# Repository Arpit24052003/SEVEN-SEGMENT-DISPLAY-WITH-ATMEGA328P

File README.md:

# SEVEN-SEGMENT-DISPLAY-WITH-ATMEGA328P
IN THIS PROJECT I HAVE INTERFACED TWO SEVEN SEGMENT DIPLAYS WITH ATEMGA328P MICROCONTROLLER.
NOTE:- THIS FILE HAS BEEN PREPARED USING AUTODESK EAGLE SO IT WILL BE COMPATIBLE WITH EAGLE ONLY

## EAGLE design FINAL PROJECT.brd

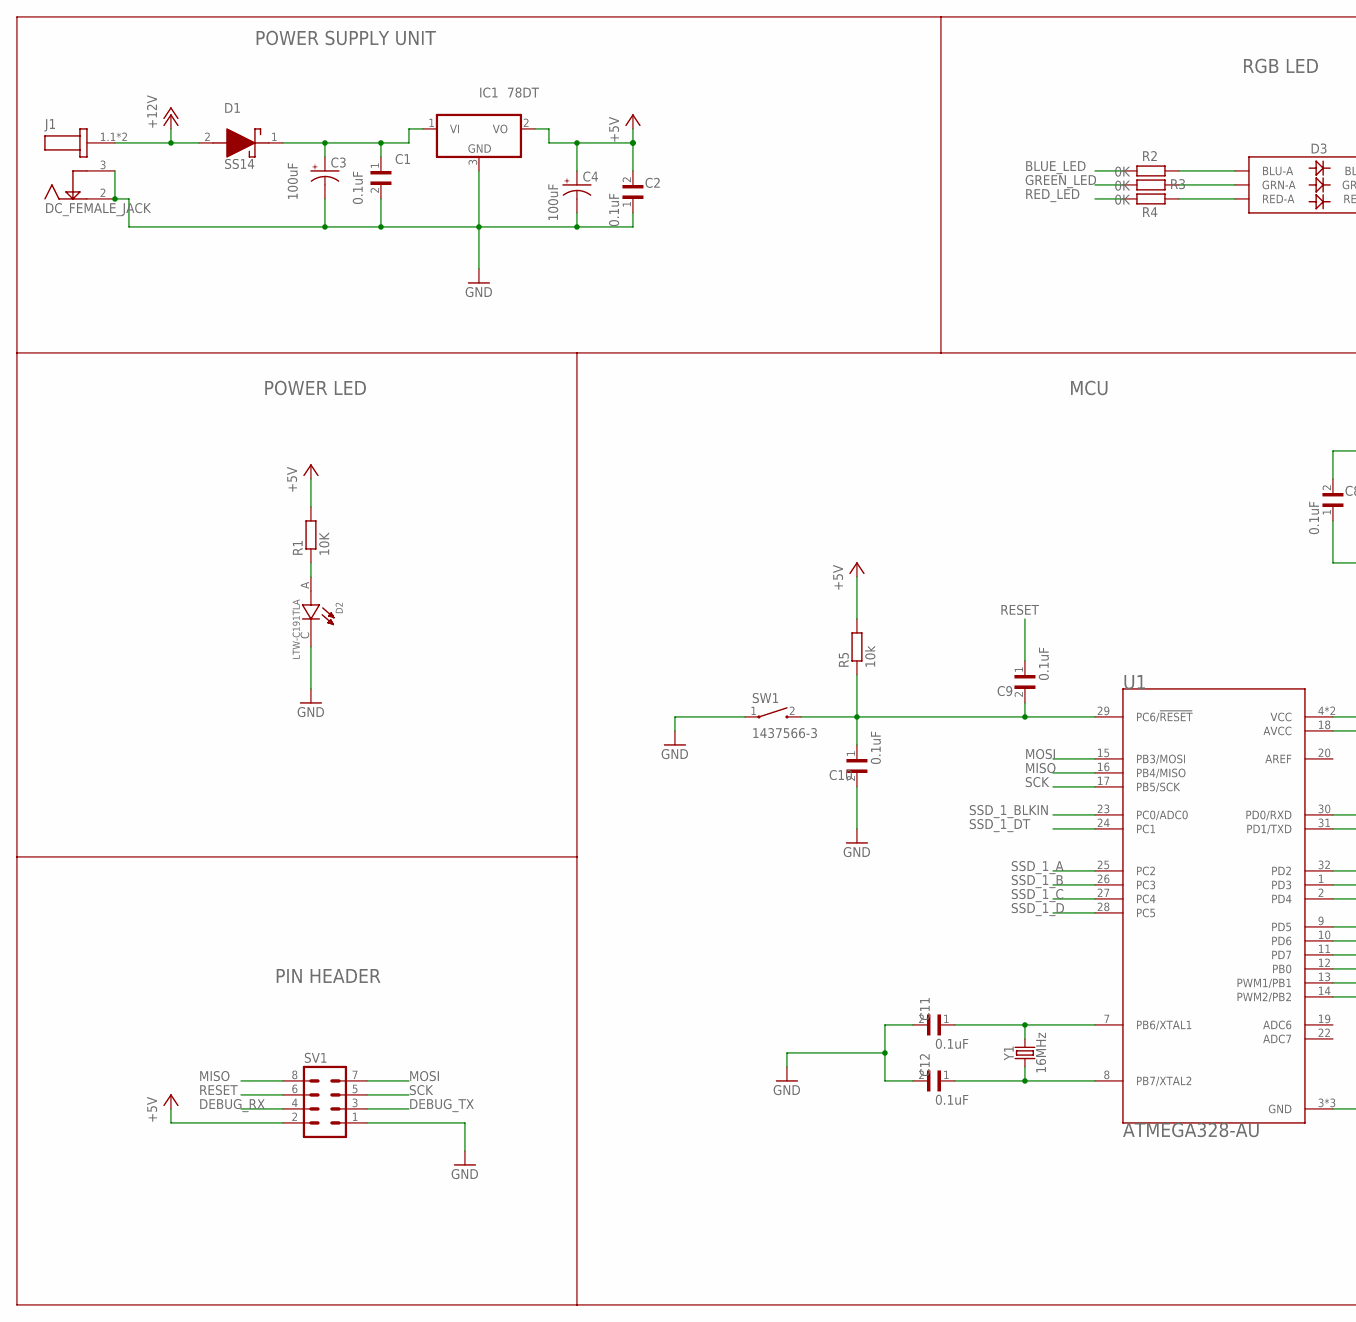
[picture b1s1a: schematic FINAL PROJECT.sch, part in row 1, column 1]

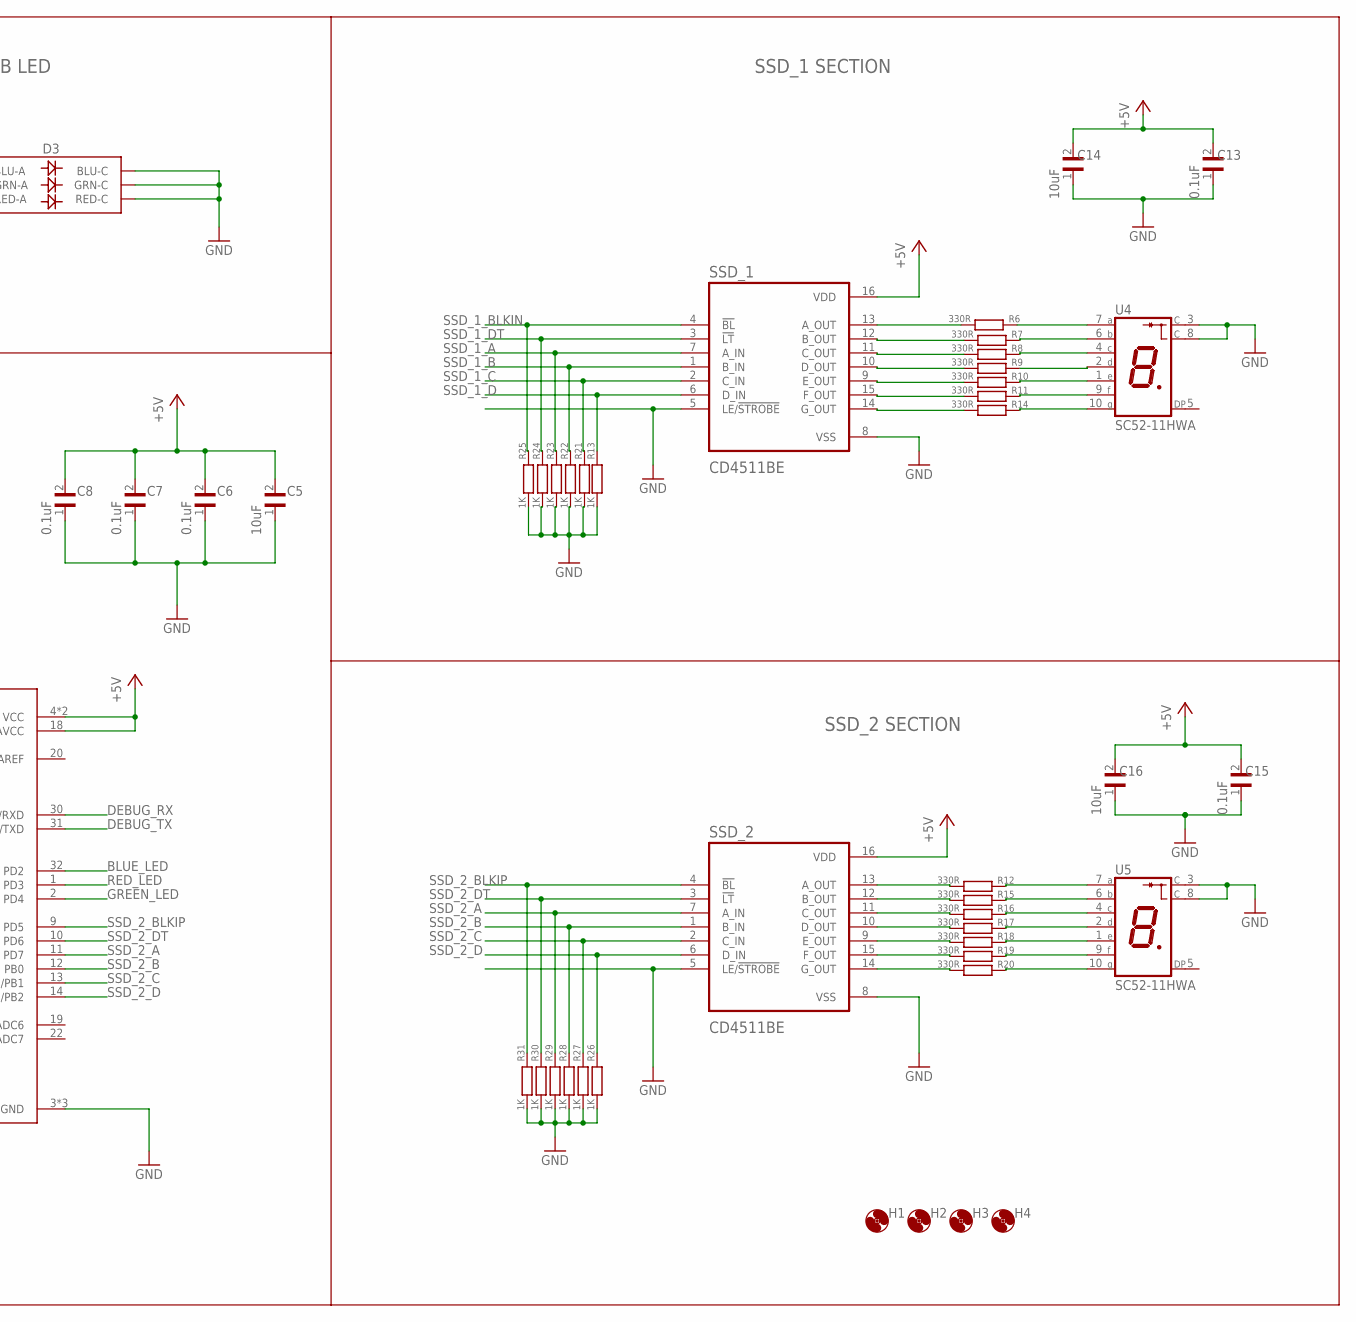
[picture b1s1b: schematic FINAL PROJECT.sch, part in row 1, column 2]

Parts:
C1, C2, C6, C7, C8, C9, C10, C11, C12, C13, C15: 0.1uF; C0603
C3, C4: 100uF; CPOL-RADIAL-2.5MM-6.5MM
C5, C14, C16: 10uF; C0603
D1: SS14; DIOM5126X250N
D2: LTW-C191TLA; LEDC1608X65N
D3: LED-RGBNO_IC; LED-TRICOLOR-5050
H1, H2, H3, H4: MOUNT-HOLE2.8; 2,8
IC1: 78DT; TO252
J1: DC_FEMALE_JACK; GCT_DCJ200-05-A-XX-X_REVA
R1: 10K; R0603
R2, R3, R4: 0K; R0603
R5: 10k; R0603
R6, R7, R8, R9, R10, R11, R12, R14, R15, R16, R17, R18, R19, R20: 330R; R0603
R13, R21, R22, R23, R24, R25, R26, R27, R28, R29, R30, R31: 1K; R0603
SSD_1, SSD_2: CD4511BE; DIP794W45P254L1969H508Q16
SV1: MA04-2
SW1: 1437566-3; SW_1437566-3
U1: ATMEGA328-AU; QFP80P900X900X120-32N
U4, U5: SC52-11HWA; LED_SC52-11HWA
Y1: 16MHz; HC49US

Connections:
+5V: C2.2, C4.1 (+), C5.2, C6.2, C7.2, C8.2, C13.2, C14.2, C15.2, C16.2, IC1.2 (VO), R1.2, R5.2, SSD_1.16 (VDD), SSD_2.16 (VDD), SV1.2, U1.4 (VCC), U1.6 (VCC), U1.18 (AVCC)
+12V: D1.2 (A), J1.1.1 (1), J1.1.2 (1)
BLUE_LED: R2.2, U1.32 (PD2)
DEBUG_RX: SV1.4, U1.30 (PD0/RXD)
DEBUG_TX: SV1.3, U1.31 (PD1/TXD)
GND: C1.2, C2.1, C3.2 (-), C4.2 (-), C5.1, C6.1, C7.1, C8.1, C10.2, C11.2, C12.2, C13.1, C14.1, C15.1, C16.1, D2.C, D3.4 (BLU-C), D3.5 (RED-C), D3.6 (GRN-C), IC1.3 (GND), J1.2, J1.3, R13.2, R21.2, R22.2, R23.2, R24.2, R25.2, R26.2, R27.2, R28.2, R29.2, R30.2, R31.2, SSD_1.5 (LE/!STROBE), SSD_1.8 (VSS), SSD_2.5 (LE/!STROBE), SSD_2.8 (VSS), SV1.1, SW1.1, U1.3 (GND), U1.5 (GND), U1.21 (GND), U4.3 (C), U4.8 (C), U5.3 (C), U5.8 (C)
GREEN_LED: R3.2, U1.2 (PD4)
MISO: SV1.8, U1.16 (PB4/MISO)
MOSI: SV1.7, U1.15 (PB3/MOSI)
unnamed: C1.1, C3.1 (+), D1.1 (K), IC1.1 (VI)
unnamed: D2.A, R1.1
unnamed: C9.2, C10.1, R5.1, SW1.2, U1.29 (PC6/!RESET)
unnamed: C11.1, U1.7 (PB6/XTAL1), Y1.2
unnamed: C12.1, U1.8 (PB7/XTAL2), Y1.1
unnamed: R6.2, SSD_1.13 (A_OUT)
unnamed: R7.2, SSD_1.12 (B_OUT)
unnamed: R8.2, SSD_1.11 (C_OUT)
unnamed: D3.3 (BLU-A), R2.1
unnamed: D3.1 (GRN-A), R3.1
unnamed: D3.2 (RED-A), R4.1
unnamed: R9.2, SSD_1.10 (D_OUT)
unnamed: R10.2, SSD_1.9 (E_OUT)
unnamed: R11.2, SSD_1.15 (F_OUT)
unnamed: R14.2, SSD_1.14 (G_OUT)
unnamed: R6.1, U4.7 (A)
unnamed: R7.1, U4.6 (B)
unnamed: R8.1, U4.4 (C)
unnamed: R9.1, U4.2 (D)
unnamed: R10.1, U4.1 (E)
unnamed: R11.1, U4.9 (F)
unnamed: R14.1, U4.10 (G)
unnamed: R15.1, U5.6 (B)
unnamed: R16.1, U5.4 (C)
unnamed: R12.2, SSD_2.13 (A_OUT)
unnamed: R15.2, SSD_2.12 (B_OUT)
unnamed: R16.2, SSD_2.11 (C_OUT)
unnamed: R17.2, SSD_2.10 (D_OUT)
unnamed: R18.2, SSD_2.9 (E_OUT)
unnamed: R19.2, SSD_2.15 (F_OUT)
unnamed: R20.2, SSD_2.14 (G_OUT)
unnamed: R12.1, U5.7 (A)
unnamed: R17.1, U5.2 (D)
unnamed: R18.1, U5.1 (E)
unnamed: R19.1, U5.9 (F)
unnamed: R20.1, U5.10 (G)
RED_LED: R4.2, U1.1 (PD3)
RESET: C9.1, SV1.6
SCK: SV1.5, U1.17 (PB5/SCK)
SSD_1_A: R23.1, SSD_1.7 (A_IN), U1.25 (PC2)
SSD_1_B: R22.1, SSD_1.1 (B_IN), U1.26 (PC3)
SSD_1_BLKIN: R25.1, SSD_1.4 (!BL), U1.23 (PC0/ADC0)
SSD_1_C: R21.1, SSD_1.2 (C_IN), U1.27 (PC4)
SSD_1_D: R13.1, SSD_1.6 (D_IN), U1.28 (PC5)
SSD_1_DT: R24.1, SSD_1.3 (!LT), U1.24 (PC1)
SSD_2_A: R29.1, SSD_2.7 (A_IN), U1.11 (PD7)
SSD_2_B: R28.1, SSD_2.1 (B_IN), U1.12 (PB0)
SSD_2_BLKIP: R31.1, SSD_2.4 (!BL), U1.9 (PD5)
SSD_2_C: R27.1, SSD_2.2 (C_IN), U1.13 (PWM1/PB1)
SSD_2_D: R26.1, SSD_2.6 (D_IN), U1.14 (PWM2/PB2)
SSD_2_DT: R30.1, SSD_2.3 (!LT), U1.10 (PD6)

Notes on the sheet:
POWER SUPPLY UNIT
POWER LED
PIN HEADER
RGB LED
MCU
SSD_1 SECTION
SSD_2 SECTION

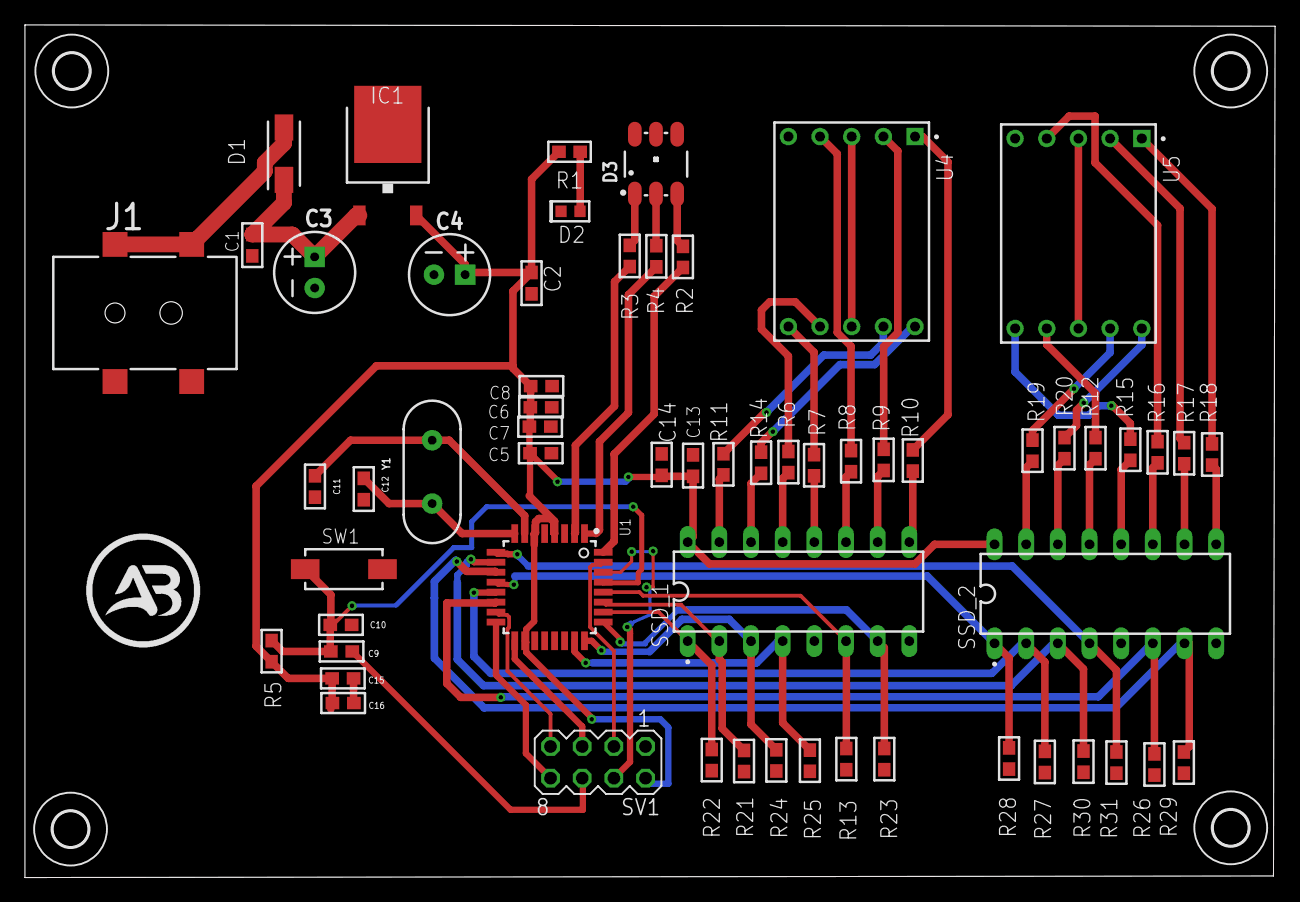
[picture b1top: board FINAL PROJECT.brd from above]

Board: 2 copper layers, 100.3 x 68.4 mm, 64 parts (0 on the bottom side), 60 nets.
